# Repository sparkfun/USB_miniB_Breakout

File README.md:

SparkFun USB Mini-B Breakout
=============================

[*SparkFun USB Mini-B Breakout (BOB-09966)*](https://www.sparkfun.com/products/9966)

This basic breakout gives the user access to all 5 miniB USB pins on a standard 0.1" header. 

Repository Contents
-------------------
* **/Hardware** - All Eagle design files (.brd, .sch)

License Information
-------------------
The hardware is released under [Creative Commons ShareAlike 4.0 International](https://creativecommons.org/licenses/by-sa/4.0/).

Distributed as-is; no warranty is given.

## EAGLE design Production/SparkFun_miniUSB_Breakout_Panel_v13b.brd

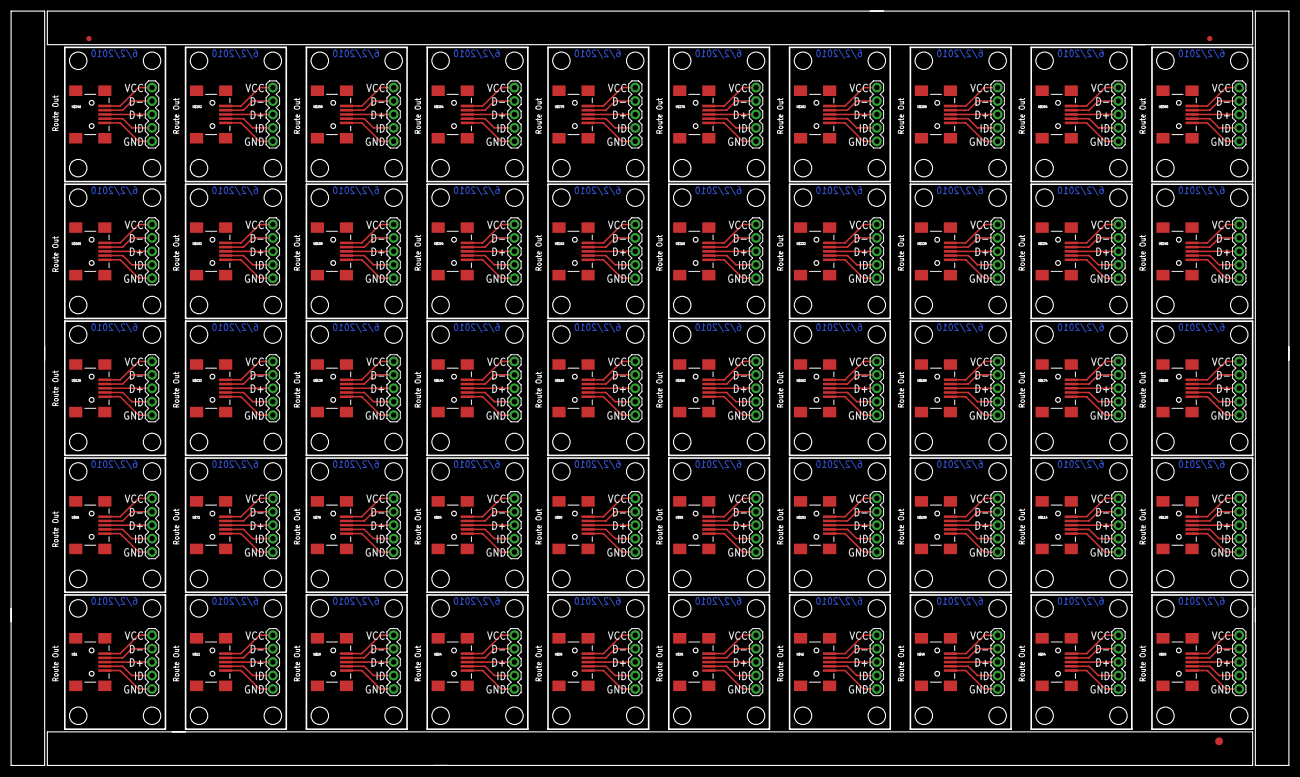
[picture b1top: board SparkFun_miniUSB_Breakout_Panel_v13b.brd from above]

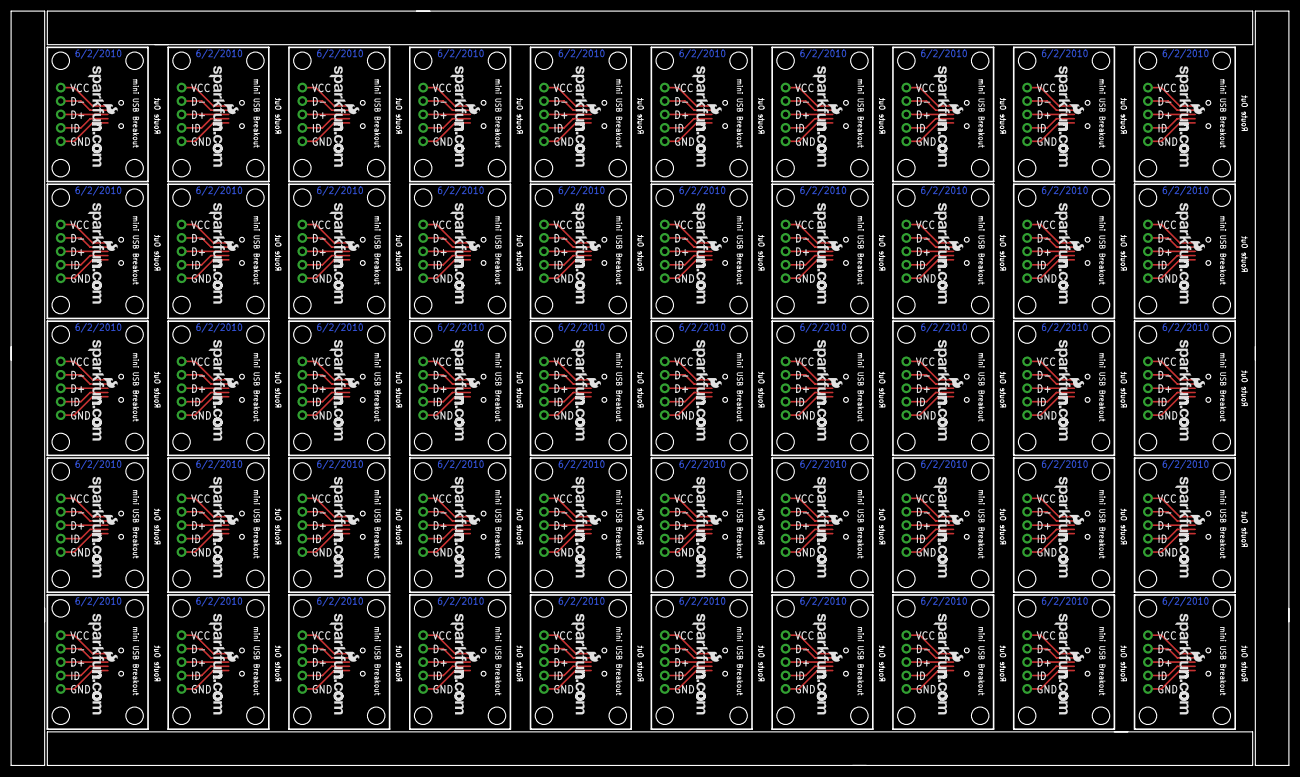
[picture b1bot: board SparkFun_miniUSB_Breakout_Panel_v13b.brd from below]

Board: 2 copper layers, 241.7 x 142.6 mm, 353 parts (50 on the bottom side), 250 nets.

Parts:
E$1: FIDUCIAL-1.5X3
E$7, E$8: FIDUCIAL-1X2
JP1, JP2, JP3, JP4, JP5, JP6, JP7, JP8, JP9, JP10, JP11, JP12, JP13, JP14, JP15, JP16, JP17, JP18, JP19, JP20, JP21, JP22, JP23, JP24, JP25, JP26, JP27, JP28, JP29, JP30, JP31, JP32, JP33, JP34, JP35, JP36, JP37, JP38, JP39, JP40, JP41, JP42, JP43, JP44, JP45, JP46, JP47, JP48, JP49, JP50: 1X05
U$1, U$12, U$18, U$24, U$30, U$36, U$42, U$48, U$54, U$60, U$66, U$72, U$78, U$84, U$90, U$96, U$102, U$108, U$114, U$120, U$126, U$132, U$138, U$144, U$150, U$156, U$162, U$168, U$174, U$180, U$186, U$192, U$198, U$204, U$210, U$216, U$222, U$228, U$234, U$240, U$246, U$252, U$258, U$264, U$270, U$276, U$282, U$288, U$294, U$300: USB-MINIB-5PIN; USB-MINIB
U$2, U$3, U$4, U$5, U$7, U$8, U$9, U$10, U$13, U$14, U$15, U$16, U$19, U$20, U$21, U$22, U$25, U$26, U$27, U$28, U$31, U$32, U$33, U$34, U$37, U$38, U$39, U$40, U$43, U$44, U$45, U$46, U$49, U$50, U$51, U$52, U$55, U$56, U$57, U$58, U$61, U$62, U$63, U$64, U$67, U$68, U$69, U$70, U$73, U$74, U$75, U$76, U$79, U$80, U$81, U$82, U$85, U$86, U$87, U$88, U$91, U$92, U$93, U$94, U$97, U$98, U$99, U$100, U$103, U$104, U$105, U$106, U$109, U$110, U$111, U$112, U$115, U$116, U$117, U$118, U$121, U$122, U$123, U$124, U$127, U$128, U$129, U$130, U$133, U$134, U$135, U$136, U$139, U$140, U$141, U$142, U$145, U$146, U$147, U$148, U$151, U$152, U$153, U$154, U$157, U$158, U$159, U$160, U$163, U$164, U$165, U$166, U$169, U$170, U$171, U$172, U$175, U$176, U$177, U$178, U$181, U$182, U$183, U$184, U$187, U$188, U$189, U$190, U$193, U$194, U$195, U$196, U$199, U$200, U$201, U$202, U$205, U$206, U$207, U$208, U$211, U$212, U$213, U$214, U$217, U$218, U$219, U$220, U$223, U$224, U$225, U$226, U$229, U$230, U$231, U$232, U$235, U$236, U$237, U$238, U$241, U$242, U$243, U$244, U$247, U$248, U$249, U$250, U$253, U$254, U$255, U$256, U$259, U$260, U$261, U$262, U$265, U$266, U$267, U$268, U$271, U$272, U$273, U$274, U$277, U$278, U$279, U$280, U$283, U$284, U$285, U$286, U$289, U$290, U$291, U$292, U$295, U$296, U$297, U$298: STAND-OFF
U$6, U$11, U$17, U$23, U$29, U$35, U$41, U$47, U$53, U$59, U$65, U$71, U$77, U$83, U$89, U$95, U$101, U$107, U$113, U$119, U$125, U$131, U$137, U$143, U$149, U$155, U$161, U$167, U$173, U$179, U$185, U$191, U$197, U$203, U$209, U$215, U$221, U$227, U$233, U$239, U$245, U$251, U$257, U$263, U$269, U$275, U$281, U$287, U$293, U$299: LOGO-SFENEW; SFE-NEW-WEBLOGO

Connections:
GND: JP1.5, U$1.GND
GND1: JP2.5, U$12.GND
GND2: JP3.5, U$18.GND
GND3: JP4.5, U$24.GND
GND4: JP5.5, U$30.GND
GND5: JP6.5, U$36.GND
GND6: JP7.5, U$42.GND
GND7: JP8.5, U$48.GND
GND8: JP9.5, U$54.GND
GND9: JP10.5, U$60.GND
GND10: JP11.5, U$66.GND
GND11: JP12.5, U$72.GND
GND12: JP13.5, U$78.GND
GND13: JP14.5, U$84.GND
GND14: JP15.5, U$90.GND
GND15: JP16.5, U$96.GND
GND16: JP17.5, U$102.GND
GND17: JP18.5, U$108.GND
GND18: JP19.5, U$114.GND
GND19: JP20.5, U$120.GND
GND20: JP21.5, U$126.GND
GND21: JP22.5, U$132.GND
GND22: JP23.5, U$138.GND
GND23: JP24.5, U$144.GND
GND24: JP25.5, U$150.GND
GND25: JP26.5, U$156.GND
GND26: JP27.5, U$162.GND
GND27: JP28.5, U$168.GND
GND28: JP29.5, U$174.GND
GND29: JP30.5, U$180.GND
GND30: JP31.5, U$186.GND
GND31: JP32.5, U$192.GND
GND32: JP33.5, U$198.GND
GND33: JP34.5, U$204.GND
GND34: JP35.5, U$210.GND
GND35: JP36.5, U$216.GND
GND36: JP37.5, U$222.GND
GND37: JP38.5, U$228.GND
GND38: JP39.5, U$234.GND
GND39: JP40.5, U$240.GND
GND40: JP41.5, U$246.GND
GND41: JP42.5, U$252.GND
GND42: JP43.5, U$258.GND
GND43: JP44.5, U$264.GND
GND44: JP45.5, U$270.GND
GND45: JP46.5, U$276.GND
GND46: JP47.5, U$282.GND
GND47: JP48.5, U$288.GND
GND48: JP49.5, U$294.GND
GND49: JP50.5, U$300.GND
unnamed: JP1.2, U$1.D-
unnamed: JP1.1, U$1.VBUS
unnamed: JP1.3, U$1.D+
unnamed: JP2.2, U$12.D-
unnamed: JP1.4, U$1.ID
unnamed: JP2.1, U$12.VBUS
unnamed: JP2.3, U$12.D+
unnamed: JP2.4, U$12.ID
unnamed: JP3.2, U$18.D-
unnamed: JP3.1, U$18.VBUS
unnamed: JP3.3, U$18.D+
unnamed: JP3.4, U$18.ID
unnamed: JP4.2, U$24.D-
unnamed: JP4.1, U$24.VBUS
unnamed: JP4.3, U$24.D+
unnamed: JP4.4, U$24.ID
unnamed: JP5.2, U$30.D-
unnamed: JP5.1, U$30.VBUS
unnamed: JP5.3, U$30.D+
unnamed: JP5.4, U$30.ID
unnamed: JP6.2, U$36.D-
unnamed: JP6.1, U$36.VBUS
unnamed: JP6.3, U$36.D+
unnamed: JP6.4, U$36.ID
unnamed: JP7.2, U$42.D-
unnamed: JP7.1, U$42.VBUS
unnamed: JP7.3, U$42.D+
unnamed: JP7.4, U$42.ID
unnamed: JP8.2, U$48.D-
unnamed: JP8.1, U$48.VBUS
unnamed: JP8.3, U$48.D+
unnamed: JP8.4, U$48.ID
unnamed: JP9.2, U$54.D-
unnamed: JP9.1, U$54.VBUS
unnamed: JP9.3, U$54.D+
unnamed: JP9.4, U$54.ID
unnamed: JP10.2, U$60.D-
unnamed: JP10.1, U$60.VBUS
unnamed: JP10.3, U$60.D+
unnamed: JP10.4, U$60.ID
unnamed: JP11.2, U$66.D-
unnamed: JP11.1, U$66.VBUS
unnamed: JP11.3, U$66.D+
unnamed: JP11.4, U$66.ID
unnamed: JP12.2, U$72.D-
unnamed: JP12.1, U$72.VBUS
unnamed: JP12.3, U$72.D+
unnamed: JP12.4, U$72.ID
unnamed: JP13.2, U$78.D-
unnamed: JP13.1, U$78.VBUS
unnamed: JP13.3, U$78.D+
unnamed: JP13.4, U$78.ID
unnamed: JP14.2, U$84.D-
unnamed: JP14.1, U$84.VBUS
unnamed: JP14.3, U$84.D+
unnamed: JP14.4, U$84.ID
unnamed: JP15.2, U$90.D-
unnamed: JP15.1, U$90.VBUS
unnamed: JP15.3, U$90.D+
unnamed: JP15.4, U$90.ID
unnamed: JP16.2, U$96.D-
unnamed: JP16.1, U$96.VBUS
unnamed: JP16.3, U$96.D+
unnamed: JP16.4, U$96.ID
unnamed: JP17.2, U$102.D-
unnamed: JP17.1, U$102.VBUS
unnamed: JP17.3, U$102.D+
unnamed: JP17.4, U$102.ID
unnamed: JP18.2, U$108.D-
unnamed: JP18.1, U$108.VBUS
unnamed: JP18.3, U$108.D+
unnamed: JP18.4, U$108.ID
unnamed: JP19.2, U$114.D-
unnamed: JP19.1, U$114.VBUS
unnamed: JP19.3, U$114.D+
unnamed: JP19.4, U$114.ID
unnamed: JP20.2, U$120.D-
unnamed: JP20.1, U$120.VBUS
unnamed: JP20.3, U$120.D+
unnamed: JP20.4, U$120.ID
unnamed: JP21.2, U$126.D-
unnamed: JP21.1, U$126.VBUS
unnamed: JP21.3, U$126.D+
unnamed: JP21.4, U$126.ID
unnamed: JP22.2, U$132.D-
unnamed: JP22.1, U$132.VBUS
unnamed: JP22.3, U$132.D+
unnamed: JP22.4, U$132.ID
unnamed: JP23.2, U$138.D-
unnamed: JP23.1, U$138.VBUS
unnamed: JP23.3, U$138.D+
unnamed: JP23.4, U$138.ID
unnamed: JP24.2, U$144.D-
unnamed: JP24.1, U$144.VBUS
unnamed: JP24.3, U$144.D+
unnamed: JP24.4, U$144.ID
unnamed: JP25.2, U$150.D-
unnamed: JP25.1, U$150.VBUS
unnamed: JP25.3, U$150.D+
unnamed: JP25.4, U$150.ID
unnamed: JP26.2, U$156.D-
unnamed: JP26.1, U$156.VBUS
unnamed: JP26.3, U$156.D+
unnamed: JP26.4, U$156.ID
unnamed: JP27.2, U$162.D-
unnamed: JP27.1, U$162.VBUS
unnamed: JP27.3, U$162.D+
unnamed: JP27.4, U$162.ID
unnamed: JP28.2, U$168.D-
unnamed: JP28.1, U$168.VBUS
unnamed: JP28.3, U$168.D+
unnamed: JP28.4, U$168.ID
unnamed: JP29.2, U$174.D-
unnamed: JP29.1, U$174.VBUS
unnamed: JP29.3, U$174.D+
unnamed: JP29.4, U$174.ID
unnamed: JP30.2, U$180.D-
unnamed: JP30.1, U$180.VBUS
unnamed: JP30.3, U$180.D+
unnamed: JP30.4, U$180.ID
unnamed: JP31.2, U$186.D-
unnamed: JP31.1, U$186.VBUS
unnamed: JP31.3, U$186.D+
unnamed: JP31.4, U$186.ID
unnamed: JP32.2, U$192.D-
unnamed: JP32.1, U$192.VBUS
unnamed: JP32.3, U$192.D+
unnamed: JP32.4, U$192.ID
unnamed: JP33.2, U$198.D-
unnamed: JP33.1, U$198.VBUS
unnamed: JP33.3, U$198.D+
unnamed: JP33.4, U$198.ID
unnamed: JP34.2, U$204.D-
unnamed: JP34.1, U$204.VBUS
unnamed: JP34.3, U$204.D+
unnamed: JP34.4, U$204.ID
unnamed: JP35.2, U$210.D-
unnamed: JP35.1, U$210.VBUS
unnamed: JP35.3, U$210.D+
unnamed: JP35.4, U$210.ID
unnamed: JP36.2, U$216.D-
unnamed: JP36.1, U$216.VBUS
unnamed: JP36.3, U$216.D+
unnamed: JP36.4, U$216.ID
unnamed: JP37.2, U$222.D-
unnamed: JP37.1, U$222.VBUS
unnamed: JP37.3, U$222.D+
unnamed: JP37.4, U$222.ID
unnamed: JP38.2, U$228.D-
unnamed: JP38.1, U$228.VBUS
unnamed: JP38.3, U$228.D+
unnamed: JP38.4, U$228.ID
unnamed: JP39.2, U$234.D-
unnamed: JP39.1, U$234.VBUS
unnamed: JP39.3, U$234.D+
unnamed: JP39.4, U$234.ID
unnamed: JP40.2, U$240.D-
unnamed: JP40.1, U$240.VBUS
unnamed: JP40.3, U$240.D+
unnamed: JP40.4, U$240.ID
unnamed: JP41.2, U$246.D-
unnamed: JP41.1, U$246.VBUS
unnamed: JP41.3, U$246.D+
unnamed: JP41.4, U$246.ID
unnamed: JP42.2, U$252.D-
unnamed: JP42.1, U$252.VBUS
unnamed: JP42.3, U$252.D+
unnamed: JP42.4, U$252.ID
unnamed: JP43.2, U$258.D-
unnamed: JP43.1, U$258.VBUS
unnamed: JP43.3, U$258.D+
unnamed: JP43.4, U$258.ID
unnamed: JP44.2, U$264.D-
unnamed: JP44.1, U$264.VBUS
unnamed: JP44.3, U$264.D+
unnamed: JP44.4, U$264.ID
unnamed: JP45.2, U$270.D-
unnamed: JP45.1, U$270.VBUS
unnamed: JP45.3, U$270.D+
unnamed: JP45.4, U$270.ID
unnamed: JP46.2, U$276.D-
unnamed: JP46.1, U$276.VBUS
unnamed: JP46.3, U$276.D+
unnamed: JP46.4, U$276.ID
unnamed: JP47.2, U$282.D-
unnamed: JP47.1, U$282.VBUS
unnamed: JP47.3, U$282.D+
unnamed: JP47.4, U$282.ID
unnamed: JP48.2, U$288.D-
unnamed: JP48.1, U$288.VBUS
unnamed: JP48.3, U$288.D+
unnamed: JP48.4, U$288.ID
unnamed: JP49.2, U$294.D-
unnamed: JP49.1, U$294.VBUS
unnamed: JP49.3, U$294.D+
unnamed: JP49.4, U$294.ID
unnamed: JP50.2, U$300.D-
unnamed: JP50.1, U$300.VBUS
unnamed: JP50.3, U$300.D+
unnamed: JP50.4, U$300.ID

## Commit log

2015-02-18 Initial hardware file commit
2015-12-17 created larger panel v13b

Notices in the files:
parts and their libraries:
SparkFun-Aesthetics: Licensing: CC v3.0 Share-Alike You are welcome to use this library for commercial purposes.
SparkFun-Retired: Licensing:Creative Commons ShareAlike 4.0 International - https://creativecommons.org/licenses/by-sa/4.0
